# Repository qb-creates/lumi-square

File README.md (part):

# LumiSquare
LumiSquare is a handheld 4x4 LED button game console built around an ATSAMD21J18A. Each of the sixteen silicone pads sits on top of its own RGB LED, and a single 16-channel constant-current driver paints all forty-eight color channels through a column-multiplexed matrix. The console ships with three games, spoken score readout through a DFPlayer Mini, a tone buzzer for note feedback, and a USB-C rechargeable power path that lets the device be played while it charges.

- Project Video (YouTube): https://youtu.be/QTP0zEY1d-M?si=SdRo0hkOKRWzujol
- Multiplexed Display: https://en.wikipedia.org/wiki/Multiplexed_display
- Keyboard Matrix Circuit (diode anti-ghosting): https://en.wikipedia.org/wiki/Keyboard_matrix_circuit
- STP16CPC05 Constant Current LED Driver: https://www.st.com/en/power-management/stp16cpc05.html
- DFPlayer Mini Documentation: https://wiki.dfrobot.com/DFPlayer_Mini_SKU_DFR0299

<div align="center">
	
</div>

## Table of Contents
1. [Software Used](#software)
2. [Main Control Board Circuit](#maincontrolboard)
    - [Power Path and Battery Charging](#powerpath)
    - [LED Button Matrix Driver](#leddriver)
    - [Button Matrix Circuit](#buttonmatrixcircuit)
    - [Buzzer Control](#buzzercontrol)
    - [DF Player Mini](#dfplayer)
    - [Game Firmware](#gamefirmware)
        - [Simon](#simon)
        - [Memory Matching](#memorymatching)
        - [Light Dash](#lightdash)
    - [Power Consumption](#powerconsumption)
    - [Charging Notes](#charging)
    - [Parts List](#partslist)
    - [Schematics](#schematics)
    - [PCB Images](#pcbimages)
3. [Pin Mapping](#pinmapping)
    - [DF Player Mini](#dfplayerpins)
    - [Buzzer](#buzzerpins)
    - [LED Mapping](#ledmapping)
    - [4x4 Button Mapping](#buttonmapping)
4. [STL Viewer](#stlviewer)
    - [Full Design](#fulldesign)
    - [Face Plate](#faceplate)
    - [Back Cover](#backcover)
    - [Main Body](#mainbody)
    - [Main Control Board](#maincontrolboardstl)

## 1. Software Used
- VSCode: https://code.visualstudio.com
- OpenOCD (Arm GDB Bridge): https://openocd.org/pages/about.html
- Arm GNU Toolchain (programming and debugging): https://developer.arm.com/tools-and-software/gnu-toolchain
- KiCad (PCB Design): https://www.kicad.org
- Autodesk Fusion (Parts Design): https://www.autodesk.com/products/fusion-360/overview

The firmware is a CMake project with two presets. `cmake_generate_debug` / `cmake_build_debug` cross compile for the SAMD21 with `arm-none-eabi-gcc` (Cortex-M0+, `F_CPU=48000000`) and emit an `.elf`, `.hex`, and `.bin`. `cmake_generate_desktop` / `cmake_build_desktop` build the same game code as a desktop executable with `DESKTOP_SIMULATION` defined, which swaps the SAMD21 hardware layer for an ImGui/GLFW/miniaudio implementation so the games, LED colors, and audio can be developed without the board. Flashing and debugging is done over the Samtec FTSH-105 SWD header using OpenOCD as the GDB bridge for `arm-none-eabi-gdb`.

## 2. Main Control Board Circuit
The main control board carries everything except the switches and LEDs themselves: the USB-C charger, the battery power path, both boost converters, the 3.3 V regulator, the SAMD21, the LED driver and its column drivers, the tone buzzer, and the DFPlayer Mini. It connects to the button matrix board through two 12-pin headers, one carrying the twelve LED cathode channels and one carrying the four button rows, four button columns, and four LED column anodes.

<div align="center">
 <table>
     <tr>
         <td></td>
         <td></td>
     </tr>
     <tr>
         <td></td>
         <td></td>
     </tr>
 </table>
</div>

### Power Path and Battery Charging
The board runs from either a single cell LiPo or USB-C, and the two sources are kept electrically separate so the device can be used while it charges.

Charging is handled by an MCP73831-2-OT (U1) off the USB-C VBUS rail. The USB-C receptacle is a power-only 6-pin part with the two 5.1k CC pulldowns (R1, R2) needed to advertise a sink. The charge current is set by the PROG resistor:

- Charge current = 1000 V / R3 = 1000 V / 10 kohm = 100 mA

A status LED (D1) with a 330 ohm series resistor (R4) is driven from the STAT pin.

The power path itself is built from two TLV61070A boost converters and a P-channel pass device:

- Q2 (IRLML2246) sits between the battery and the battery-side boost converter. Its gate is tied to the 5 V USB rail and pulled to ground through R11 (220k). With no USB present the gate sits at 0 V and the MOSFET conducts; when USB is plugged in the gate is pulled to 5 V and the battery is disconnected from the system load.
- U3 (TLV61070A) is the battery boost converter. Its enable pin is pulled up to the battery through R6 (150k) and is gated two ways: a TPS3840 (U2) supervisor pulls it low on battery undervoltage, and Q1 (IRLML6244) pulls it low whenever the 5 V USB rail is present.
- U4 (TLV61070A) is the USB boost converter. Its enable pin is tied to its own input, so it runs whenever USB power is present.
- Both converters use a 4.7uH inductor and the same 720k/80k feedback divider, and their outputs are combined onto the 5.3 V rail through Schottky diodes (D2, D3, 1N5819HW-7-F) with 300uF of bulk capacitance (C8, C9, C10).

Downstream of the 5.3 V rail, SW1 is the system power switch feeding a MIC5225-3.3YM5 (U8) that produces the +3.3 V Main rail for the SAMD21, the DFPlayer Mini, and the buzzer. The 5.3 V rail itself powers the LED column drivers, so the RGB LEDs get their headroom from the boost output rather than the regulated logic rail.

### LED Button Matrix Driver
Sixteen common-anode RGB LEDs are driven as a 4x4 multiplexed matrix. Anodes are shared per column, and cathodes are shared per row and color, which reduces forty-eight LED channels down to twelve driver channels plus four column selects.

The cathode side is an STP16CPC05MTR (U6) constant-current sink. Twelve of its sixteen channels are used, one for each row and color combination, and a 200 ohm resistor (R12) on R-EXT sets the per-channel current for all of them. The MCU talks to it over SERCOM4 in SPI master mode (MSB first, 16 bits per update), with a separate GPIO line used to pulse the latch.

The anode side is a high-side switch per column. Each column select from the MCU drives an MMBT3904 (Q4-Q7) through a 2.2k base resistor with a 47k pulldown; the transistor pulls the gate of a TSM680P06CH P-channel MOSFET (Q15-Q18) down against a 100k pullup to the 5.3 V rail, and the MOSFET drain feeds that column's anode line.

Color depth comes from binary code modulation rather than a per-channel PWM peripheral. Each LED stores its color as eight bit planes in `ledColorData[column][row][plane]`. `refreshLeds()` services one LED per call: it enables that LED's column, then shifts out all eight planes back to back, holding plane *i* for 2^i NOP loops so the planes carry the same weighting as the bits of an 8-bit value. After the last plane the driver is cleared to `0x0000` and the next LED index is selected. Only one column ever sources current at a time, and the sixteen LED slots repeat fast enough that the display looks continuous.

Per-LED intensity is a scale from 0 to 1 applied to the color before the bit planes are rebuilt, so the games can dim a pad (the idle Simon pads sit at 0.2 intensity, for example) without changing its color.

### Button Matrix Circuit
The button matrix board holds the sixteen switches, the sixteen RGB LEDs, and nothing else. Switches are wired as a standard 4x4 matrix with a 1N4148 diode in series with every switch (D1-D16) so that simultaneous presses cannot ghost onto unrelated rows. The MCU drives one column low at a time and reads the four row inputs, which are held high by internal pullups, so a pressed button reads as a logic low on its row while its column is active.

The LEDs on this board are wired to match. Anodes are commoned per column (LED_COL1 through LED_COL4) and cathodes are commoned per row and color (LED_R1/G1/B1 through LED_R4/G4/B4). Both groups leave the board on 12-pin headers that mate with the main control board.

**Assembly notes for the button pad:**

- The 4x4 silicone button pad in the parts list is not the right size for this enclosure. The individual pads have to be cut out of the sheet and placed into the pockets in the face plate.
- If you have the button matrix board fabricated, order it with an immersion gold (ENIG) finish. The exposed contact pads need a gold surface for the conductive pill on the bottom of each silicone button to make reliable contact.
- If the board is made with a plain finish instead, buy the copper tape listed in the parts list and adhere a piece to the bottom of each button pad so that the button can bridge the traces.

### Buzzer Control
Tones are produced by a magnetic transducer (BZ2, RDT-4.000-1375-NS1) switched on the low side by an MMBT3904 (Q8). The base is driven through a 2.2k resistor (R22) from the MCU, and a 1N4148W (D4) across the transducer clamps the inductive kickback back into the +3.3 V rail.

The drive signal is hardware PWM from TC7 on PB23. TC7 runs from the 48 MHz main clock with a divide-by-256 prescaler in match PWM mode:

- Timer clock = 48 MHz / 256 = 187.5 kHz
- Output frequency = 187500 / (CC0 + 1)
- `CC1` is always set to `CC0 / 2`, which holds the duty cycle at 50 percent regardless of pitch

Because the period register alone determines pitch, the `MusicNote` enum stores CC0 values directly instead of frequencies. For example `MusicNote::C4 = 716`, which gives 187500 / 717 = 261.5 Hz. Starting and stopping a note is just enabling or disabling the timer, so note timing stays exact while the game loop is busy elsewhere.

### DF Player Mini
Spoken audio comes from a DFPlayer Mini (DFR0299) running off the +3.3 V rail, with its speaker outputs broken out to a JST connector. The module is driven from SERCOM5 in USART mode on PA20/PA21 at 9600 baud.

Every DFPlayer command is a fixed 10-byte frame (`0x7E 0xFF 0x06 <cmd> 0x00 <param hi> <param lo> <checksum hi> <checksum lo> 0xEF`). Rather than building those frames at runtime, the firmware stores all of them precomputed in a constant table, so playing a clip is a table lookup. Frames are pushed out by DMAC channel 0 triggered off the SERCOM5 transmit event, one beat per trigger, so the game loop never blocks on the UART.

Replies come back through the SERCOM5 receive interrupt, which buffers the module's 20-byte response (the command acknowledgement plus the playback-finished frame) and fires a completion callback when the terminating `0xEF` arrives. That callback is what advances queued voice-over sequences, which is how the console reads a multi-digit score back as separate clips.

Audio content is organized into four folders on the SD card, and the command table plays from them by folder and track number:

| Folder | Contents |
|:--|:--|
| 01 | Digits 0 through 9 |
| 02 | 10 through 20, then 30, 40, 50, 60, 70, 80, 90 |
| 03 | 100, 200, 300, 400, 500 |
| 04 | Phrases: "your score is", "new high score", the game names, the difficulty names, countdown, mute, unmute |

To read a score such as 342, the firmware queues the hundreds clip, then the tens clip, then the ones clip, and lets the completion callback chain them together. Volume is set with command `0x06`; the unmute command sends a value of 25, and muting sends a value of 0.

### Game Firmware
The firmware is a fixed-timestep game engine. TC3 runs from the 48 MHz clock with a divide-by-1024 prescaler and is preloaded so it overflows every 16 ms, giving a 62.5 Hz update rate. The main loop looks like this:

```cpp
while (true)
{
    LEDMatrix::refreshLeds();

    if (!DeviceUtility::fixedUpdate)
        continue;

    DeviceUtility::fixedUpdate = false;
    Input::pollButtons();

    StateManager::Instance().onFixedUpdate();
    AudioSource::Instance().onFixedUpdate();
    ShutdownUtility::Instance().onFixedUpdate();
    SerialCommandManager::Instance().onFixedUpdate();
}
```

LED refresh runs as fast as the CPU allows, while everything else is gated on the 16 ms tick. All game timers are expressed in milliseconds and decremented by `DeviceUtility::DELTA_TIME`, so game speed is independent of how quickly the LED refresh happens to be running.

All hardware access goes through an abstract `DeviceUtility` singleton. `SAMD21J18Utility` implements it against the real peripherals, and `DesktopUtility` implements the same interface with ImGui, GLFW, and miniaudio. Every layer above it (games, LED matrix, input, audio, scoring) is shared between the two builds.

Game flow is a state machine. `StateManager` holds one instance of each state and dispatches `enterState`, `updateState`, `exitState`, and `onButtonPressed` to whichever one is current:

| State | Purpose |
|:--|:--|
| PowerOn | Startup animation and audio |
| Menu | Game selection, difficulty selection, mute toggle, start countdown |
| MemoryMatching | Color pair matching game |
| Simon | Sequence memorization game |
| LightDash | Timed reaction game |
| GameOver | Score readout and high score announcement |

In the menu, the Next and Previous buttons cycle through the three games and the Difficulty button cycles Easy, Medium, Hard. Holding the Difficulty button for one second toggles mute instead of changing difficulty, and the new mute state is announced through the DFPlayer. Selecting a game plays a spoken 3-2-1 countdown before the state switch.

`ScoreManager` tracks the current score and a high score per game and per difficulty in a 6x3 matrix. Persistence is handled by `StorageService`, which keeps high scores in the SAMD21's own flash instead of an external EEPROM. The linker script carves the last 1 KB of the 256 KB flash out of the `rom` region and gives it its own memory region:

```
rom      (rx)  : ORIGIN = 0x00000000, LENGTH = 0x0003FC00
eeprom   (rx)  : ORIGIN = 0x0003FC00, LENGTH = 0x00000400
```

A matching `.eeprom` output section is mapped into that region, and the high score array is placed there with `__attribute__((__section__(".eeprom")))`, so the linker will never let program code grow into the saved data. Each high score is a single byte addressed by game and difficulty: Memory Matching at offset 0, Simon at offset 6, Light Dash at offset 12, plus the difficulty index. A byte that has never been written reads back as `0xFF` and is reported as a score of zero.

Reading a high score is a direct pointer dereference into that flash region. Writing has to respect the SAMD21's flash granularity, so saving one byte means copying the surrounding 256-byte row into RAM, patching the byte, erasing the row through NVMCTRL, and writing all four 64-byte pages back. The read and write bodies are commented out in `StorageService` at the moment, so high scores currently live in RAM until they are re-enabled.

#### Simon
The console plays a growing sequence of lit pads with a distinct note per pad, and the player repeats it. Only eight of the sixteen pads are playable. On Easy the four center pads are used (indexes 5, 6, 9, 10); on Medium and Hard the four corners (0, 3, 12, 15) are added. Each playable pad has a fixed note assignment:

| Pad Index | Note | Pad Index | Note |
|:--:|:--:|:--:|:--:|
| 5 | G4 | 4 | A4 |
| 6 | C4 | 7 | D4 |
| 9 | E4 | 8 | F4 |
| 10 | G3 | 11 | B3 |

The player gets three lives on Easy and Medium and a single life on Hard. Idle pads sit at 0.2 intensity and the active pad steps up to full intensity for each sequence element, so the sequence reads clearly without the board going dark between steps.

#### Memory Matching
Eight color pairs are shuffled across the sixteen pads at the start of the round. Pressing a pad lights it in its hidden color; pressing a second pad evaluates the guess. Matched pairs stay lit, mismatched pads fade back off after a short reveal timer, and the round ends once all eight matches are found. Selection and evaluation are confirmed with C5 and D5 tones.

#### Light Dash
A 30 second timed reaction round. Five pads start lit in turquoise, and every lit pad carries its own randomized turn-off timer. Hitting a lit pad scores a point and immediately lights a new random pad; hitting a dark pad deducts points and plays a low B3. Difficulty changes the pressure directly:

| Difficulty | LED Turn-Off Window | Score Deduction | Bonus Pad Value | Bonus Window | Power-Ups |
|:--|:--:|:--:|:--:|:--:|:--:|
| Easy | 1500 - 2500 ms | -1 | 5 | 400 ms | Disabled |
| Medium | 1000 - 2000 ms | -2 | 3 | 500 ms | Enabled |
| Hard | 750 - 1200 ms | -3 | 5 | 400 ms | Enabled |

### Power Consumption
This power system was sized around continuous play with the LED matrix, the DFPlayer Mini, and the buzzer all active, measured on the finished assembly rather than estimated from datasheet maximums.

Measured load envelope:

- USB input, playing while charging: ~170 mA typical, 200 mA maximum
- Battery draw with USB disconnected: ~100 mA typical, 120 mA maximum
- Programmed battery charge current (MCP73831 with a 10k PROG resistor): 100 mA

The USB figure is the total of both jobs at once: the system load through the USB boost converter plus the 100 mA going into the battery. Against the 500 mA available from a standard USB port:

- Worst-case USB draw: 0.20 A of the 0.50 A available
- Remaining headroom: 0.30 A, roughly 40 percent port utilization

Battery capability and runtime with a 750 mAh single cell LiPo:

- Typical: 750 mAh / 100 mA = 7.5 h
- Worst case: 750 mAh / 120 mA = 6.25 h

That works out to roughly 6 to 7.5 hours of continuous play per charge, with the practical number landing near the low end of that range because the boost converter draws more input current as the cell voltage falls toward its cutoff. A full recharge from empty at 100 mA takes about 8 hours once the constant-voltage taper at the end of the charge cycle is included.

Conclusion: the USB port has roughly 300 mA of unused headroom even in the worst case, so charging and full-brightness play can happen at the same time without exceeding what a standard port supplies.

### Charging Notes
The device can be safely used while charging due to its power-path design. When USB power is connected, the battery-powered boost converter is disabled and the battery is isolated from the system load, allowing it to charge independently at 100 mA. The system is powered through a separate boost converter from USB power during this time. Since the combined system load and charging current remain well below the 500 mA available from a standard USB port, normal operation can continue while the battery is charging.

---
### Parts List
<div align="center">
    <table>
        <tr>
            <td valign="top">
                <table>
                    <tr><th>Part Number</th><th>Quantity</th></tr>
                    <tr><td><a href="https://www.amazon.com/dp/B0B21B262L?ref=ppx_yo2ov_dt_b_fed_asin_title&amp;th=1">4.2V Lipo</a></td><td align="center">x1</td></tr>
                    <tr><td><a href="https://www.digikey.com/en/products/detail/jst-sales-america-inc/S2B-PH-SM4-TB/926655">S2B-PH-SM4-TB</a></td><td align="center">x1</td></tr>
                    <tr><td><a href="https://www.digikey.com/en/products/detail/raltron-electronics/RDT-4-000-1375-NS1/22320849">RDT-4.000-1375-NS1</a></td><td align="center">x1</td></tr>
                    <tr><td><a href="https://www.digikey.com/en/products/detail/samsung-electro-mechanics/CL10A475KP8NNNC/3886702">4.7uF Capacitor</a></td><td align="center">x2</td></tr>
                    <tr><td><a href="https://www.digikey.com/en/products/detail/kyocera-avx/TPCL105M010R5000/1472496">1uF Tantalum Capacitor</a></td><td align="center">x3</td></tr>
                    <tr><td><a href="https://www.digikey.com/en/products/detail/taiyo-yuden/TMK107B7105KA-T/2714162">1uF Capacitor</a></td><td align="center">x2</td></tr>
                    <tr><td><a href="https://www.digikey.com/en/products/detail/murata-electronics/GCM31CR71C106KA64K/2592432">10uF Capacitor</a></td><td align="center">x2</td></tr>
                    <tr><td><a href="https://www.digikey.com/en/products/detail/murata-electronics/GCM31CR70J226ME23L/2592428">22uF Capacitor</a></td><td align="center">x2</td></tr>
                    <tr><td><a href="https://www.digikey.com/en/products/detail/kyocera-avx/TAJC107K010RNJ/563809">100uF Capacitor</a></td><td align="center">x3</td></tr>
                    <tr><td><a href="https://www.digikey.com/en/products/detail/kemet/C0603C102K5RACTU/411081">.001uF Capacitor</a></td><td align="center">x1</td></tr>
                    <tr><td><a href="https://www.digikey.com/en/products/detail/kemet/C0603C103K5RACTU/411090">.01uF Capacitor</a></td><td align="center">x1</td></tr>
                    <tr><td><a href="https://www.digikey.com/en/products/detail/kemet/C0603C104K3RACTU/416044">.1uF Capacitor</a></td><td align="center">x6</td></tr>
                    <tr><td><a href="https://www.digikey.com/en/products/detail/murata-electronics/GRM188R61E225KA12D/4905349">2.2uF Capacitor</a></td><td align="center">x1</td></tr>
                    <tr><td>LED</td><td align="center">x2</td></tr>
                    <tr><td><a href="https://www.digikey.com/en/products/detail/diodes-incorporated/1N5819HW-7-F/814970">1N5819HW-7-F Diode</a></td><td align="center">x2</td></tr>
                    <tr><td><a href="https://www.digikey.com/en/products/detail/smc-diode-solutions/1N4148W/6022450">1N4148W Diode</a></td><td align="center">x1</td></tr>
                    <tr><td><a href="https://www.amazon.com/2-54mm-Breakaway-Female-Connector-Arduino/dp/B01MQ48T2V/ref=sr_1_2_sspa?crid=16L90K4M3IPUJ&amp;dib=eyJ2IjoiMSJ9.PiVZGqfONIcta-M5ftDeSQvccVRmw9BxQL2rt7zLLUlXX1aAbZE0DyQvFnNRSX7J1oJEA5hJfbgi6EJ3rHkMxb469SjCBiPbG4t4CkfheX_9W7Yiw4iFecXODu6yRoJ7FvokpWTZ5C9jK1dhZLU-0gXDsoVq96wH-NXO7UmstsQCzrZOSzCfbpis861lxSzX91fkbaxrOKRMrX-EQ3cjwH1Og4xyfn4PJ6o445uHR2s.cW7WMcxh5mXZc1T8bR0I8nLIh45-W5JJZGus4sUdDDI&amp;dib_tag=se&amp;keywords=Male+headers&amp;qid=1783892715&amp;sprefix=male+header%2Caps%2C141&amp;sr=8-2-spons&amp;sp_csd=d2lkZ2V0TmFtZT1zcF9hdGY&amp;psc=1">Conn_01x12</a></td><td align="center">x2</td></tr>
                    <tr><td><a href="https://www.digikey.com/en/products/detail/gct/USB4125-GF-A/13547388">USB_C_Receptacle_PowerOnly_6P</a></td><td align="center">x1</td></tr>
                    <tr><td><a href="https://www.digikey.com/en/products/detail/samtec-inc/FTSH-105-01-L-DV-K/1875039">FTSH-105-01-X-DV-P-K-X</a></td><td align="center">x1</td></tr>
                    <tr><td><a href="https://www.digikey.com/en/products/detail/bourns-inc/SRP3020TA-4R7M/9350997">4.7uH</a></td><td align="center">x2</td></tr>
                    <tr><td><a href="https://www.digikey.com/en/products/detail/infineon-technologies/IRLML6244TRPBF/2393871">IRLML6244</a></td><td align="center">x1</td></tr>
                    <tr><td><a href="https://www.digikey.com/en/products/detail/umw/UMWIRLML2246TR/24889419">UMWIRLML2246TRCT</a></td><td align="center">x2</td></tr>
                    <tr><td><a href="https://www.digikey.com/en/products/detail/onsemi/MMBT3904LT1G/919601">MMBT3904</a></td><td align="center">x5</td></tr>
                    <tr><td><a href="https://www.digikey.com/en/products/detail/taiwan-semiconductor-corporation/TSM680P06CH-X0G/7360503">TSM680P06CH</a></td><td align="center">x4</td></tr>
                    <tr><td><a href="https://www.digikey.com/en/products/detail/yageo/RC0603FR-075K1L/727268">5.1k ohm Resistor</a></td><td align="center">x2</td></tr>
                    <tr><td><a href="https://www.digikey.com/en/products/detail/stackpole-electronics-inc/RMCF0603JT10K0/1758104">10k ohm Resistor</a></td><td align="center">x2</td></tr>
                    <tr><td><a href="https://www.digikey.com/en/products/detail/yageo/RC0603FR-07330RL/727162">330 ohm Resistor</a></td><td align="center">x2</td></tr>
                    <tr><td><a href="https://www.digikey.com/en/products/detail/yageo/RC0603JR-071K3L/726686">1.3k ohm Resistor</a></td><td align="center">x1</td></tr>
                    <tr><td><a href="https://www.digikey.com/en/products/detail/koa-speer-electronics-inc/RK73B1JTTD154J/9844780">150k ohm Resistor</a></td><td align="center">x1</td></tr>
                </table>
            </td>
            <td width="24"></td>
            <td valign="top">
                <table>
                    <tr><th>Part Number</th><th>Quantity</th></tr>
                    <tr><td><a href="https://www.digikey.com/en/products/detail/yageo/RC0603FR-07715KL/727372">720k ohm Resistor</a></td><td align="center">x2</td></tr>
                    <tr><td><a href="https://www.digikey.com/en/products/detail/yageo/RC0603JR-0775KL/726828">80k ohm Resistor</a></td><td align="center">x2</td></tr>
                    <tr><td><a href="https://www.digikey.com/en/products/detail/stackpole-electronics-inc/RMCF0603FT220K/1760805">220k ohm Resistor</a></td><td align="center">x1</td></tr>
                    <tr><td><a href="https://www.digikey.com/en/products/detail/rohm-semiconductor/ESR03EZPF2000/1983436">200 ohm Resistor</a></td><td align="center">x1</td></tr>
                    <tr><td><a href="https://www.digikey.com/en/products/detail/yageo/RC0603FR-07100KL/726889">100k ohm Resistor</a></td><td align="center">x5</td></tr>
                    <tr><td><a href="https://www.digikey.com/en/products/detail/panasonic-industry/ERA-3AEB153V/1465882">15k ohm Resistor</a></td><td align="center">x3</td></tr>
                    <tr><td><a href="https://www.digikey.com/en/products/detail/yageo/RC0603FR-072K2L/727016">2.2k ohm Resistor</a></td><td align="center">x5</td></tr>
                    <tr><td><a href="https://www.digikey.com/en/products/detail/yageo/RC0603FR-0747KL/727253">47k ohm Resistor</a></td><td align="center">x4</td></tr>
                    <tr><td><a href="https://www.amazon.com/2-54mm-Breakaway-Female-Connector-Arduino/dp/B01MQ48T2V/ref=sr_1_2_sspa?crid=16L90K4M3IPUJ&amp;dib=eyJ2IjoiMSJ9.PiVZGqfONIcta-M5ftDeSQvccVRmw9BxQL2rt7zLLUlXX1aAbZE0DyQvFnNRSX7J1oJEA5hJfbgi6EJ3rHkMxb469SjCBiPbG4t4CkfheX_9W7Yiw4iFecXODu6yRoJ7FvokpWTZ5C9jK1dhZLU-0gXDsoVq96wH-NXO7UmstsQCzrZOSzCfbpis861lxSzX91fkbaxrOKRMrX-EQ3cjwH1Og4xyfn4PJ6o445uHR2s.cW7WMcxh5mXZc1T8bR0I8nLIh45-W5JJZGus4sUdDDI&amp;dib_tag=se&amp;keywords=Male+headers&amp;qid=1783892715&amp;sprefix=male+header%2Caps%2C141&amp;sr=8-2-spons&amp;sp_csd=d2lkZ2V0TmFtZT1zcF9hdGY&amp;psc=1">SW_SPST</a></td><td align="center">x1</td></tr>
                    <tr><td><a href="https://www.digikey.com/en/products/detail/jst-sales-america-inc/SM02B-NSHSS-TB/3313627">SM02B-NSHSS-TB</a></td><td align="center">x1</td></tr>
                    <tr><td><a href="https://www.amazon.com/dp/B0FD32HBD2?ref=ppx_yo2ov_dt_b_fed_asin_title">JST SH 1.0mm 2-Pin Connector Male</a></td><td align="center">x6</td></tr>
                    <tr><td><a href="https://www.digikey.com/en/products/detail/jst-sales-america-inc/BM02B-SRSS-TB/926694">455-1788-1-ND</a></td><td align="center">x6</td></tr>
                    <tr><td><a href="https://www.digikey.com/en/products/detail/e-switch/TL3342F260QG/4029402">TL3342F260QG</a></td><td align="center">x1</td></tr>
                    <tr><td><a href="https://www.amazon.com/dp/B07FS9CLHB?ref=ppx_yo2ov_dt_b_fed_asin_title">SW_Push</a></td><td align="center">x3</td></tr>
                    <tr><td><a href="https://www.digikey.com/en/products/detail/microchip-technology/MCP73831T-4ADI-OT/1874437">MCP73831-2-OT</a></td><td align="center">x1</td></tr>
                    <tr><td><a href="https://www.digikey.com/en/products/detail/texas-instruments/TPS3840DL35DBVR/15857118">TPS3840</a></td><td align="center">x1</td></tr>
                    <tr><td><a href="https://www.digikey.com/en/products/detail/texas-instruments/TLV61070ADBVR/16982069">TLV61070A</a></td><td align="center">x2</td></tr>
                    <tr><td><a href="https://www.digikey.com/en/products/detail/microchip-technology/ATSAMD21J18A-AUT/4878863">ATSAMD21J18A-A</a></td><td align="center">x1</td></tr>
                    <tr><td><a href="https://www.digikey.com/en/products/detail/stmicroelectronics/STP16CPC05MTR/2021162">STP16CPC05MTR</a></td><td align="center">x1</td></tr>
                    <tr><td><a href="https://www.digikey.com/en/products/detail/microchip-technology/MIC5225-3-3YM5-TR/1815447">MIC5225-3.3YM5</a></td><td align="center">x1</td></tr>
                    <tr><td><a href="https://www.amazon.com/dp/B09YGDQV3Z?ref=ppx_yo2ov_dt_b_fed_asin_title&amp;th=1">Speaker</a></td><td align="center">x1</td></tr>
                    <tr><td><a href="https://www.amazon.com/HiLetgo-Arduino-Player-Module-DFPlayer/dp/B01D1D0E7Q/ref=sr_1_2_sspa?crid=1M2VND5DUGHIK&amp;dib=eyJ2IjoiMSJ9.YrXsgIIjUaSsAEXykz_XhedAiNLuph_OWmxQmAavccnvR6je_SPV6UBJCTTjR1HUEWpdZX6tAgtMeH9srEe7P_8sLd3BhB1FnESxTUJ68ddGd1M1iRmT9N21VSjNgaNmsWCMiqy5aJ65WuFNIvULsRhTw6QEZZM6lOIUVj8uBlg-XCqs1zCrPYvssHCZ58nAGFlbAthMA-R4jTEtol9RGDQelZQMH3D_3LqgZeJn3uU.FTGOfaaoE_vI-eDcVBTyS0GOEBdRKrRR-P7t4EqJue8&amp;dib_tag=se&amp;keywords=dfplayer+mini&amp;qid=1783881948&amp;sprefix=dfplayermini%2Caps%2C240&amp;sr=8-2-spons&amp;sp_csd=d2lkZ2V0TmFtZT1zcF9hdGY&amp;psc=1">DFPLayerMini</a></td><td align="center">x1</td></tr>
                    <tr><td><a href="https://www.sparkfun.com/button-pad-4x4-led-compatible.html">Button Pad</a></td><td align="center">x1</td></tr>
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
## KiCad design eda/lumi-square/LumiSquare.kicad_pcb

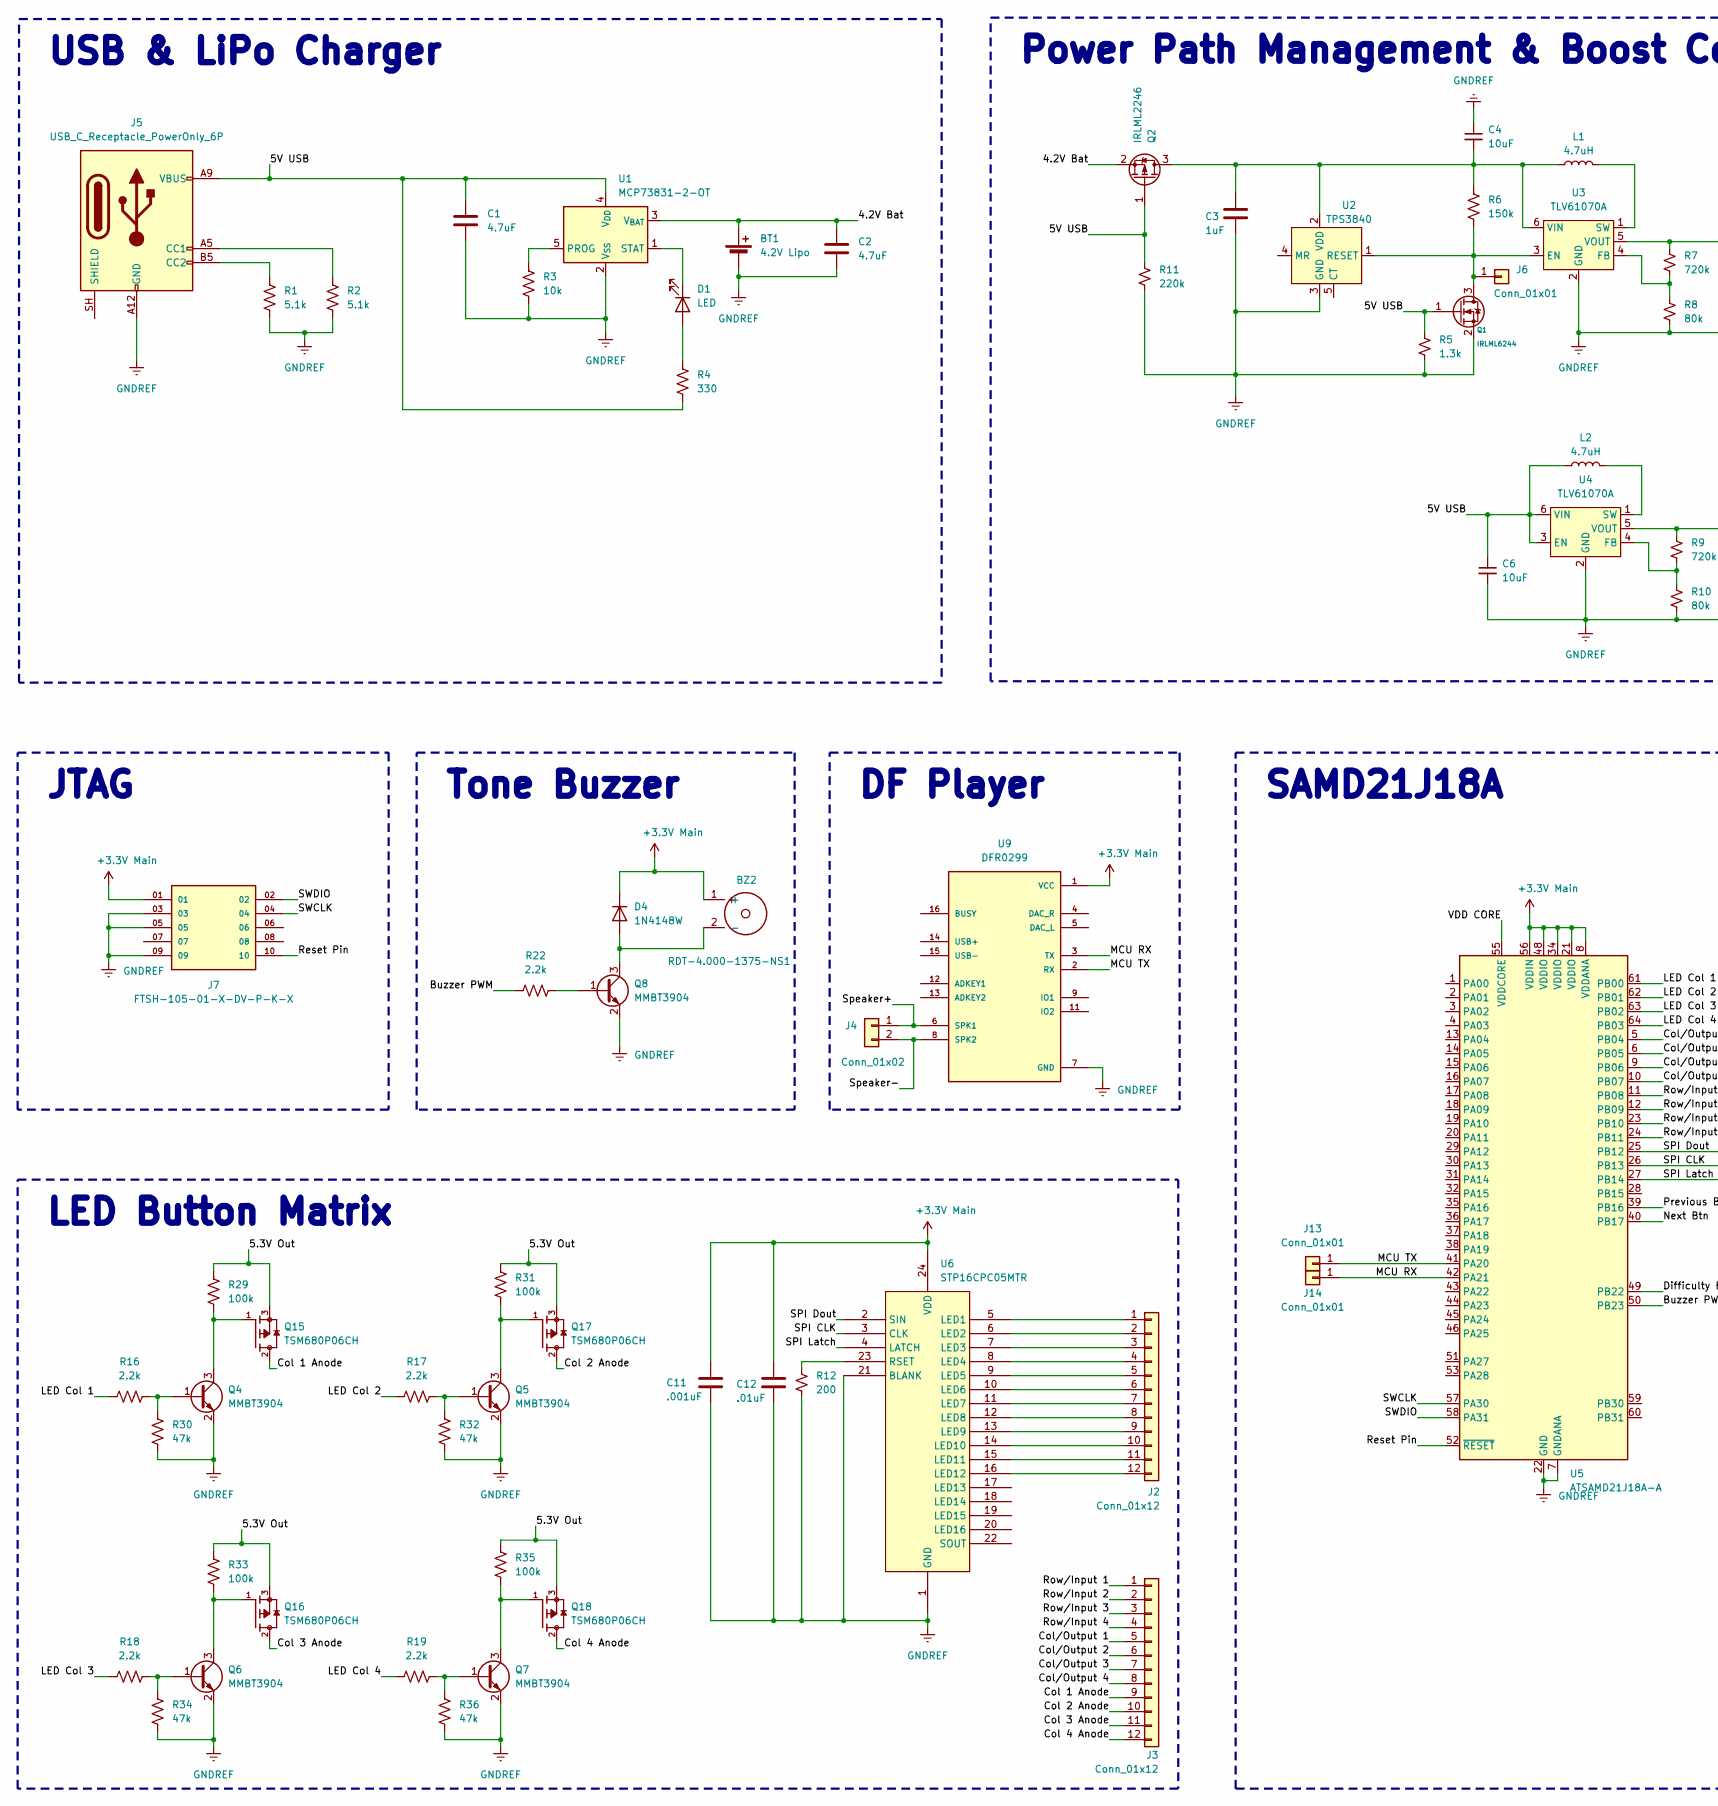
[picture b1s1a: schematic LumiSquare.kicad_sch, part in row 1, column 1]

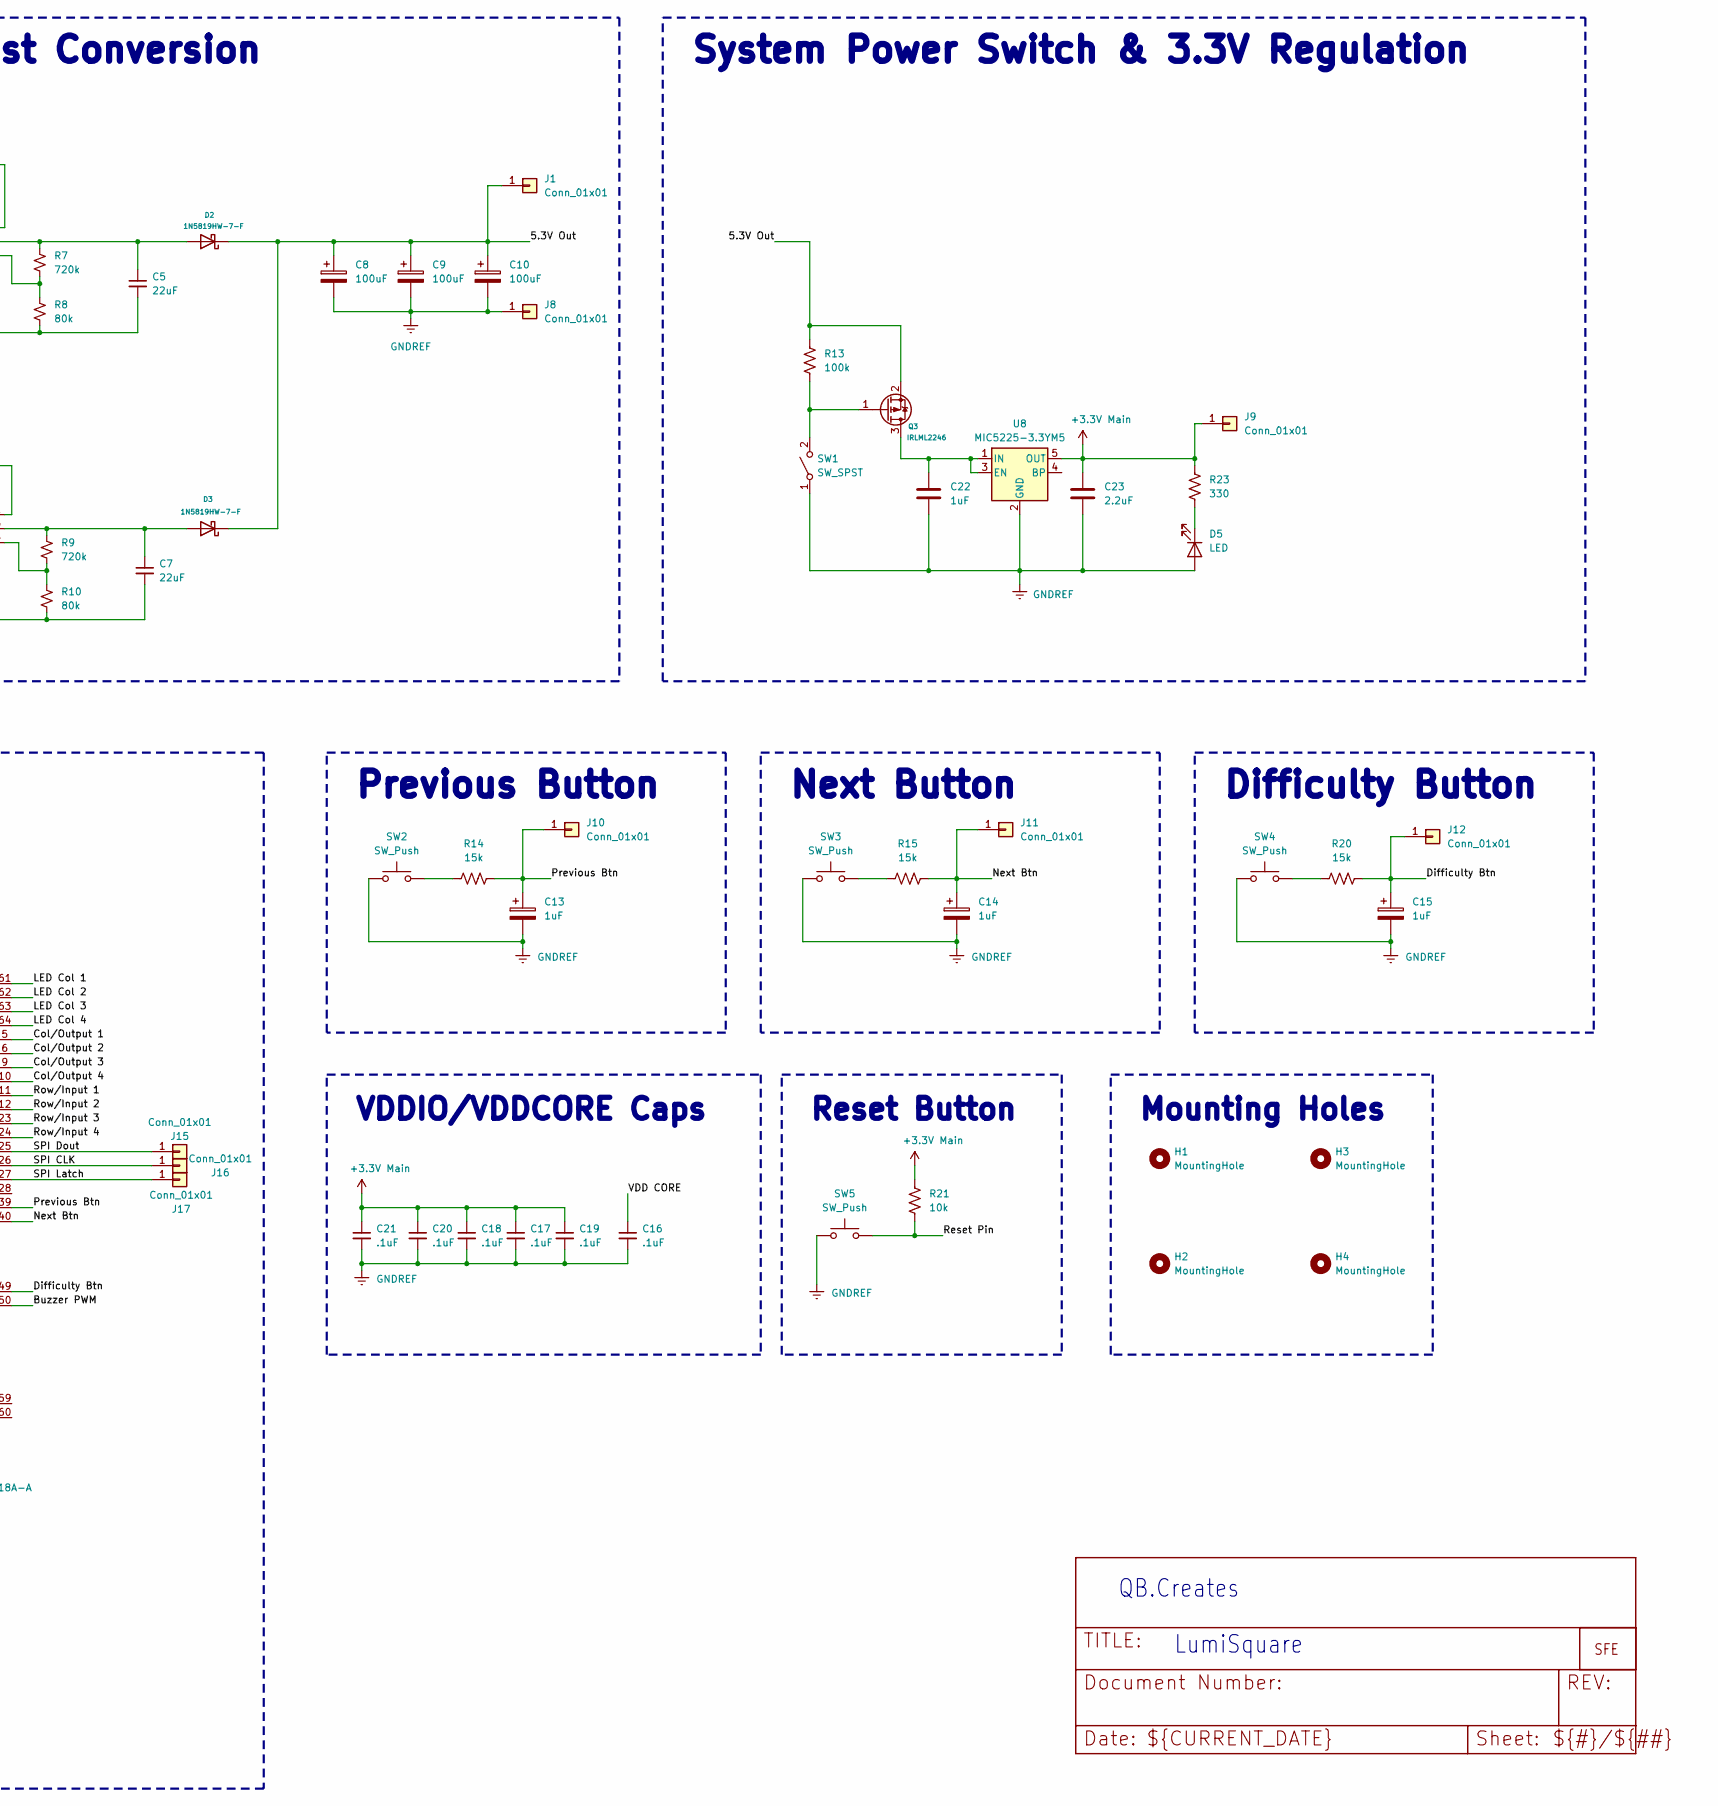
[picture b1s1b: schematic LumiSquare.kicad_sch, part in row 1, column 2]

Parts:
BT1: 4.2V Lipo; JST_PH_S2B-PH-SM4-TB_1x02-1MP_P2.00mm_Horizontal
BZ2: RDT-4.000-1375-NS1
C1, C2: 4.7uF; C_0603_1608Metric_Pad1.08x0.95mm_HandSolder
C3, C13, C14, C15, C22: 1uF; C_0603_1608Metric_Pad1.08x0.95mm_HandSolder
C4, C6: 10uF; C_1206_3216Metric
C5, C7: 22uF; C_1206_3216Metric
C8, C9, C10: 100uF; CP_EIA-6032-28_Kemet-C_HandSolder
C11: .001uF; C_0603_1608Metric_Pad1.08x0.95mm_HandSolder
C12: .01uF; C_0603_1608Metric_Pad1.08x0.95mm_HandSolder
C16, C17, C18, C19, C20, C21: .1uF; C_0603_1608Metric_Pad1.08x0.95mm_HandSolder
C23: 2.2uF; C_0603_1608Metric_Pad1.08x0.95mm_HandSolder
D1, D5: LED; JST_SH_BM02B-SRSS-TB_1x02-1MP_P1.00mm_Vertical
D2, D3: 1N5819HW-7-F; D_SOD-123
D4: 1N4148W; D_SOD-123
H1, H2, H3, H4: MountingHole; MountingHole_2.2mm_M2_DIN965_Pad
J1, J6, J8, J9, J10, J11, J12, J13, J14, J15, J16, J17: Conn_01x01; TestPoint_Pad_D1.0mm
J2, J3: Conn_01x12; PinSocket_1x12_P2.54mm_Vertical
J4: Conn_01x02; JST_SH_SM02B-SRSS-TB_1x02-1MP_P1.00mm_Horizontal
J5: USB_C_Receptacle_PowerOnly_6P; USB_C_Receptacle_GCT_USB4125-xx-x-0190_6P_TopMnt_Horizontal
J7: FTSH-105-01-X-DV-P-K-X; SAMTEC_FTSH-105-01-X-DV-P-K-X; PARTREV H
L1, L2: 4.7uH; Bourns SRP30xx
Q1: IRLML6244; SOT-23
Q2, Q3: IRLML2246; SOT-23
Q4, Q5, Q6, Q7, Q8: MMBT3904; SOT-23
Q15, Q16, Q17, Q18: TSM680P06CH; TO228P680X245X847-3; PARTREV D14
R1, R2: 5.1k; R_0603_1608Metric_Pad0.98x0.95mm_HandSolder
R3, R21: 10k; R_0603_1608Metric_Pad0.98x0.95mm_HandSolder
R4, R23: 330; R_0603_1608Metric_Pad0.98x0.95mm_HandSolder
R5: 1.3k; R_0603_1608Metric_Pad0.98x0.95mm_HandSolder
R6: 150k; R_0603_1608Metric_Pad0.98x0.95mm_HandSolder
R7, R9: 720k; R_0603_1608Metric_Pad0.98x0.95mm_HandSolder
R8, R10: 80k; R_0603_1608Metric
R11: 220k; R_0603_1608Metric_Pad0.98x0.95mm_HandSolder
R12: 200; R_0603_1608Metric_Pad0.98x0.95mm_HandSolder
R13, R29, R31, R33, R35: 100k; R_0603_1608Metric_Pad0.98x0.95mm_HandSolder
R14, R15, R20: 15k; R_0603_1608Metric_Pad0.98x0.95mm_HandSolder
R16, R17, R18, R19, R22: 2.2k; R_0603_1608Metric_Pad0.98x0.95mm_HandSolder
R30, R32, R34, R36: 47k; R_0603_1608Metric_Pad0.98x0.95mm_HandSolder
SW1: SW_SPST; JST_SH_BM02B-SRSS-TB_1x02-1MP_P1.00mm_Vertical
SW2, SW3, SW4: SW_Push; JST_SH_BM02B-SRSS-TB_1x02-1MP_P1.00mm_Vertical
SW5: SW_Push; SW_SPST_TL3342
U1: MCP73831-2-OT; SOT-23-5
U2: TPS3840; SOT-23-5
U3, U4: TLV61070A; SOT-23-6
U5: ATSAMD21J18A-A; TQFP-64_10x10mm_P0.5mm
U6: STP16CPC05MTR; SOIC-24W_7.5x15.4mm_P1.27mm
U8: MIC5225-3.3YM5; SOT-23-5
U9: DFR0299; MODULE_DFR0299
U$1: LOGO-SFE; SFE-NEW-WEBLOGO

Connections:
+3.3V Main: BZ2.1 (+), C11.1, C12.1, C17.1, C18.1, C19.1, C20.1, C21.1, C23.1, D4.1 (K), J7.01, J9.1 (Pin_1_1), R21.1, R23.2, U5.8 (VDDANA), U5.21 (VDDIO), U5.34 (VDDIO), U5.48 (VDDIO), U5.56 (VDDIN), U6.24 (VDD), U8.5 (OUT), U9.1 (VCC)
/4.2V Bat: BT1.1 (+), C2.1, Q2.2 (S), U1.3 (V_{BAT})
/5.3V Out: C8.1, C9.1, C10.1, D2.1 (K), D3.1 (K), J1.1 (Pin_1_1), Q3.2 (S), Q15.3, Q16.3, Q17.3, Q18.3, R13.1, R29.2, R31.2, R33.2, R35.2
/5V USB: C1.1, C6.1, J5.A9 (VBUS), J5.B9 (VBUS), L2.1, Q1.1 (G), Q2.1 (G), R4.1, R5.1, R11.1, U1.4 (V_{DD}), U4.3 (EN), U4.6 (VIN)
/Buzzer PWM: R22.1, U5.50 (PB23)
/Col 1 Anode: J3.9, Q15.2
/Col 2 Anode: J3.10, Q17.2
/Col 3 Anode: J3.11, Q16.2
/Col 4 Anode: J3.12, Q18.2
/Col/Output 1: J3.5, U5.5 (PB04)
/Col/Output 2: J3.6, U5.6 (PB05)
/Col/Output 3: J3.7, U5.9 (PB06)
/Col/Output 4: J3.8, U5.10 (PB07)
/Difficulty Btn: C15.1, J12.1 (Pin_1_1), R20.2, U5.49 (PB22)
/LED Col 1: R16.1, U5.61 (PB00)
/LED Col 2: R17.1, U5.62 (PB01)
/LED Col 3: R18.1, U5.63 (PB02)
/LED Col 4: R19.1, U5.64 (PB03)
/MCU RX: J14.1 (Pin_1_1), U5.42 (PA21), U9.3 (TX)
/MCU TX: J13.1 (Pin_1_1), U5.41 (PA20), U9.2 (RX)
/Next Btn: C14.1, J11.1 (Pin_1_1), R15.2, U5.40 (PB17)
/Previous Btn: C13.1, J10.1 (Pin_1_1), R14.2, U5.39 (PB16)
/Reset Pin: J7.10, R21.2, SW5.2, U5.52 (~RESET)
/Row/Input 1: J3.1, U5.11 (PB08)
/Row/Input 2: J3.2, U5.12 (PB09)
/Row/Input 3: J3.3, U5.23 (PB10)
/Row/Input 4: J3.4, U5.24 (PB11)
/SPI CLK: J16.1 (Pin_1_1), U5.26 (PB13), U6.3 (CLK)
/SPI Dout: J15.1 (Pin_1_1), U5.25 (PB12), U6.2 (SIN)
/SPI Latch: J17.1 (Pin_1_1), U5.27 (PB14), U6.4 (LATCH)
/SWCLK: J7.04, U5.57 (PA30)
/SWDIO: J7.02, U5.58 (PA31)
/Speaker+: J4.1, U9.6 (SPK1)
/Speaker-: J4.2, U9.8 (SPK2)
/VDD CORE: C16.1, U5.55 (VDDCORE)
GNDREF: BT1.2 (-), C1.2, C2.2, C3.2, C4.1, C5.2, C6.2, C7.2, C8.2, C9.2, C10.2, C11.2, C12.2, C13.2, C14.2, C15.2, C16.2, C17.2, C18.2, C19.2, C20.2, C21.2, C22.2, C23.2, D5.2 (A), J5.A12 (GND), J5.B12 (GND), J7.03, J7.05, J7.09, J8.1 (Pin_1_1), Q1.2 (S), Q4.2 (E), Q5.2 (E), Q6.2 (E), Q7.2 (E), Q8.2 (E), R1.2, R2.2, R3.2, R5.2, R8.2, R10.2, R11.2, R12.2, R30.1, R32.1, R34.1, R36.1, SW1.1 (A), SW2.1, SW3.1, SW4.1, SW5.1, U1.2 (V_{SS}), U2.3 (GND), U3.2 (GND), U4.2 (GND), U5.7 (GNDANA), U5.22 (GND), U5.33 (GND), U5.47 (GND), U5.54 (GND), U6.1 (GND), U6.21 (BLANK), U8.2 (GND), U9.7 (GND), U9.10 (GND)
unnamed: BZ2.2 (-), D4.2 (A), Q8.3 (C)
unnamed: D1.2 (A), R4.2
unnamed: D1.1 (K), U1.1 (STAT)
unnamed: C5.1, D2.2 (A), R7.1, U3.5 (VOUT)
unnamed: C7.1, D3.2 (A), R9.1, U4.5 (VOUT)
unnamed: D5.1 (K), R23.1
unnamed: J2.1, U6.5 (LED1)
unnamed: J2.2, U6.6 (LED2)
unnamed: J2.3, U6.7 (LED3)
unnamed: J2.4, U6.8 (LED4)
unnamed: J2.5, U6.9 (LED5)
unnamed: J2.6, U6.10 (LED6)
unnamed: J2.7, U6.11 (LED7)
unnamed: J2.8, U6.12 (LED8)
unnamed: J2.9, U6.13 (LED9)
unnamed: J2.10, U6.14 (LED10)
unnamed: J2.11, U6.15 (LED11)
unnamed: J2.12, U6.16 (LED12)
unnamed: J5.A5 (CC1), R2.1
unnamed: J5.B5 (CC2), R1.1
unnamed: J6.1 (Pin_1_1), Q1.3 (D), R6.2, U2.1 (RESET), U3.3 (EN)
unnamed: C3.1, C4.2, L1.1, Q2.3 (D), R6.1, U2.2 (VDD), U3.6 (VIN)
unnamed: C22.1, Q3.3 (D), U8.1 (IN), U8.3 (EN)
unnamed: Q3.1 (G), R13.2, SW1.2 (B)
unnamed: Q4.1 (B), R16.2, R30.2
unnamed: Q4.3 (C), Q15.1, R29.1
unnamed: Q5.1 (B), R17.2, R32.2
unnamed: Q5.3 (C), Q17.1, R31.1
unnamed: Q6.1 (B), R18.2, R34.2
unnamed: Q6.3 (C), Q16.1, R33.1
unnamed: Q7.1 (B), R19.2, R36.2
unnamed: Q7.3 (C), Q18.1, R35.1
unnamed: Q8.1 (B), R22.2
unnamed: R14.1, SW2.2
unnamed: R15.1, SW3.2
unnamed: R20.1, SW4.2
unnamed: R3.1, U1.5 (PROG)
unnamed: R7.2, R8.1, U3.4 (FB)
unnamed: L1.2, U3.1 (SW)
unnamed: R9.2, R10.1, U4.4 (FB)
unnamed: L2.2, U4.1 (SW)
unnamed: R12.1, U6.23 (RSET)

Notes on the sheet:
USB & LiPo Charger
SAMD21J18A
Mounting Holes
VDDIO/VDDCORE Caps
Reset Button
DF Player
Power Path Management & Boost Conversion
Tone Buzzer
Next Button
System Power Switch & 3.3V Regulation
LumiSquare
Previous Button
JTAG
QB.Creates
LED Button Matrix
Difficulty Button

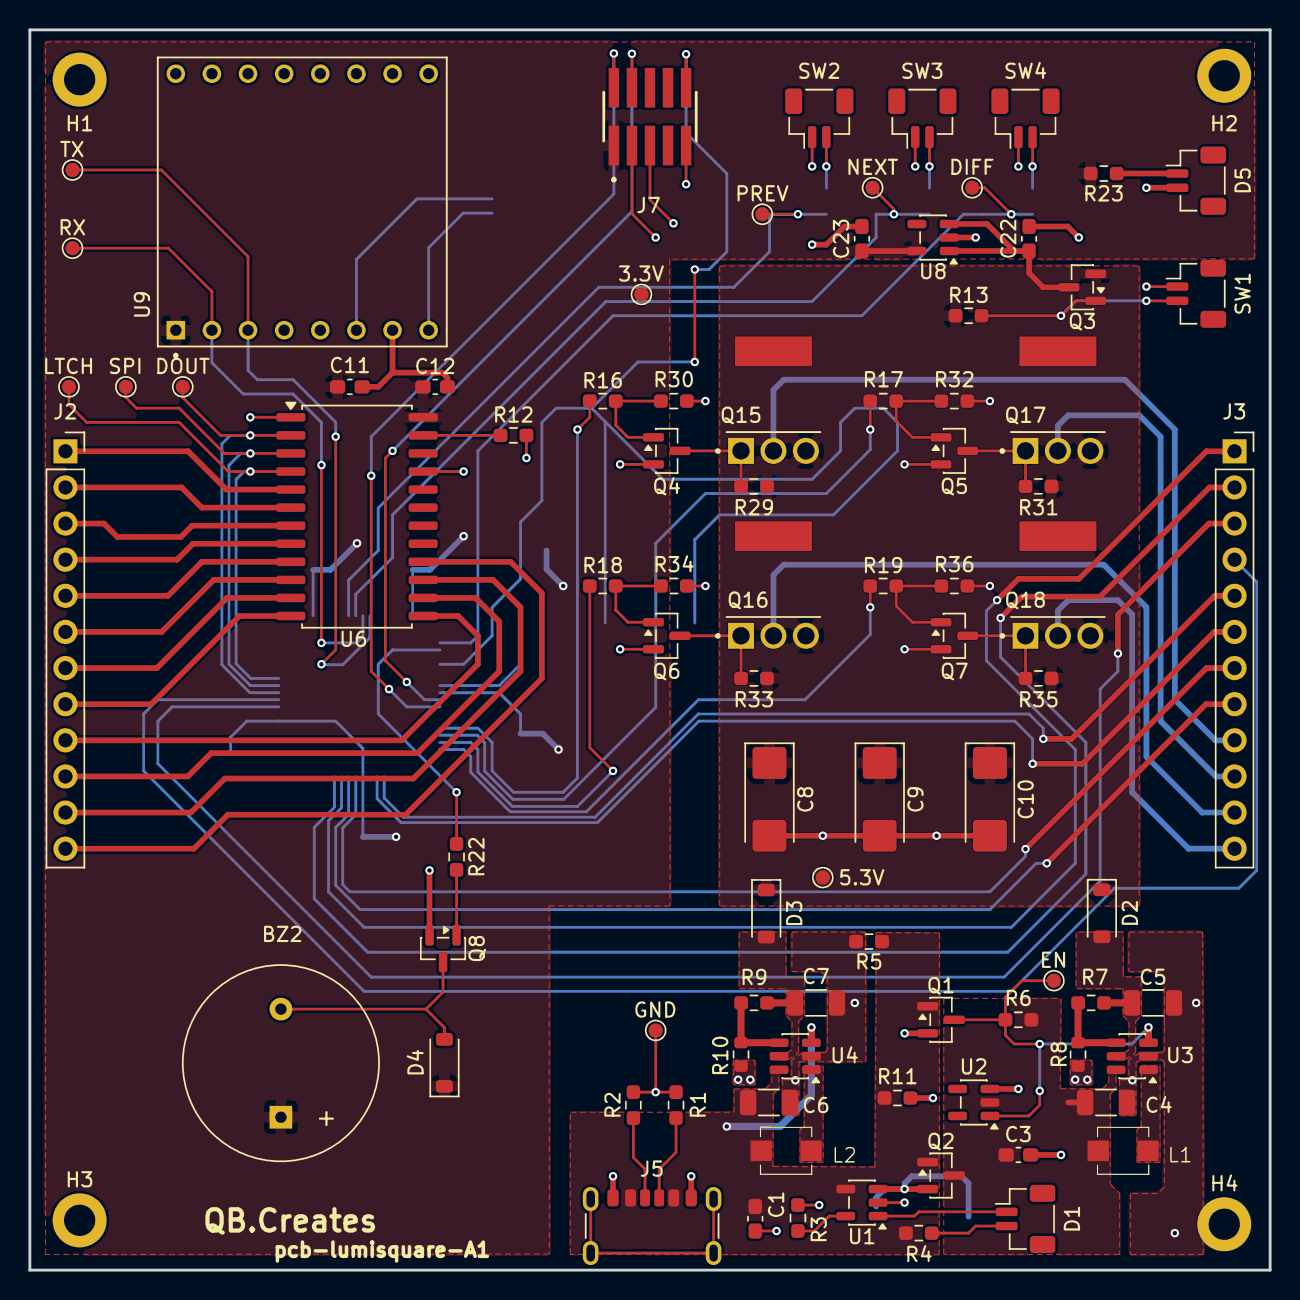
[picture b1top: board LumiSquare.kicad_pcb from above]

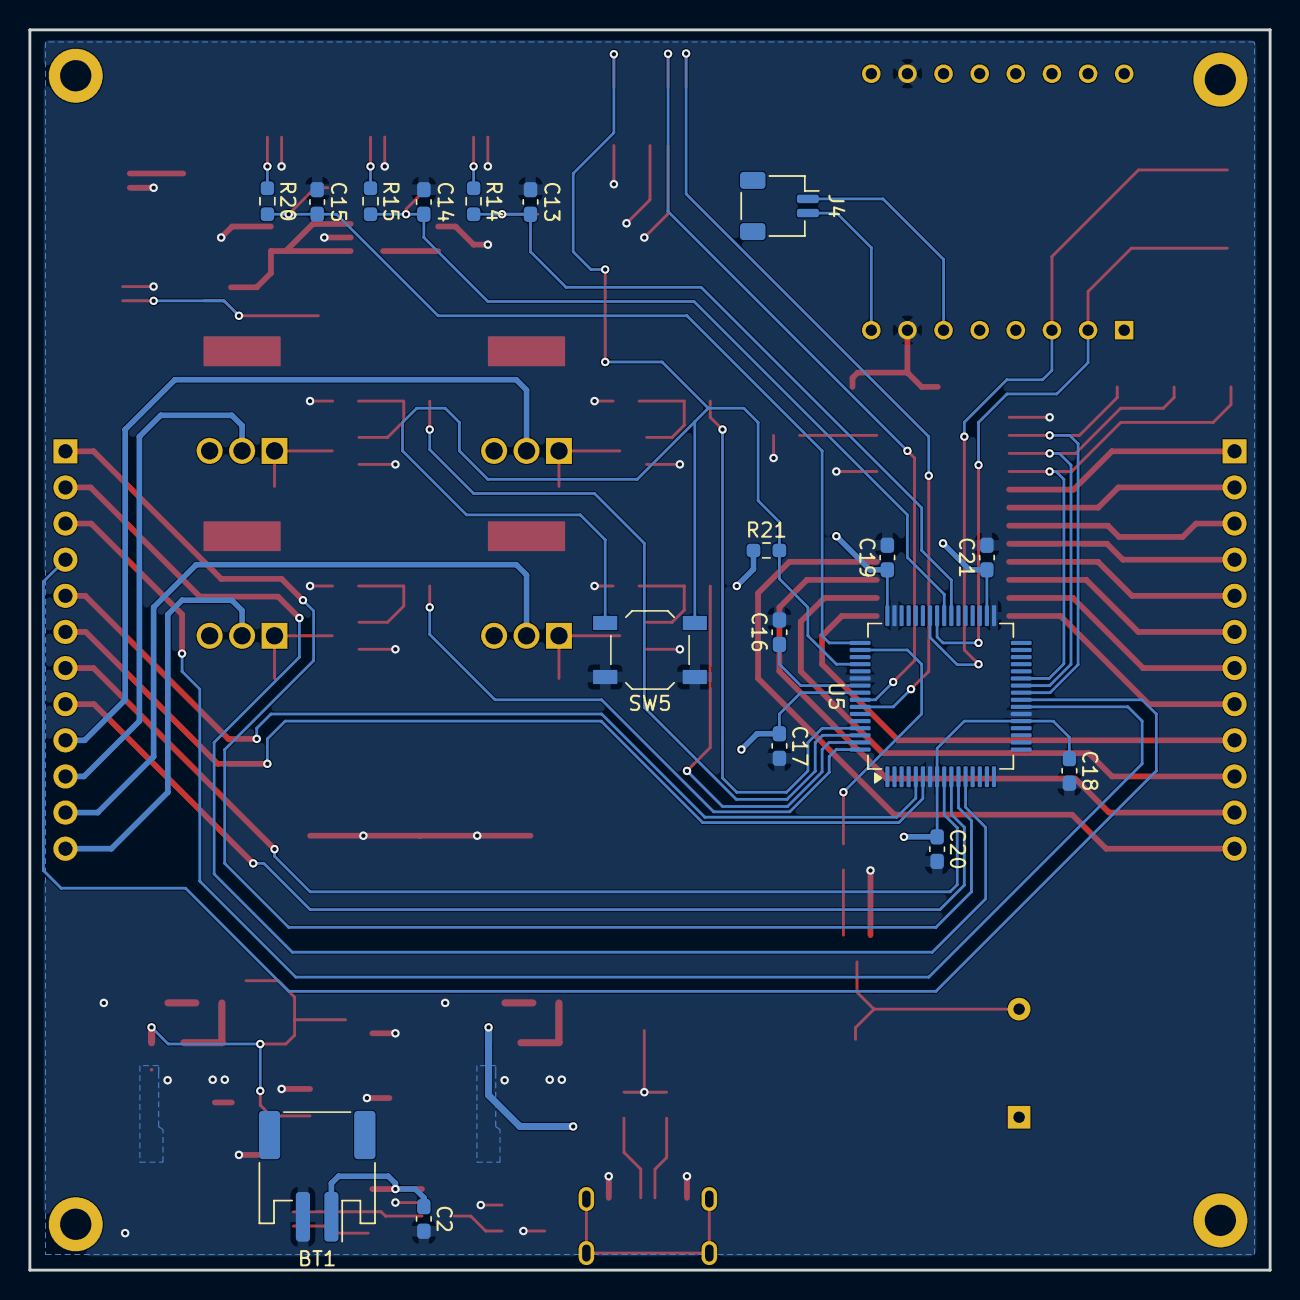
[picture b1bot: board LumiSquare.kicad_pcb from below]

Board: 2 copper layers, 87.2 x 87.2 mm, 109 parts (18 on the bottom side), 78 nets.

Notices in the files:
README.md:
License:
See [LICENSE](LICENSE) for details.
| | `CC0` sets the period and therefore the pitch: frequency = 187500 / (CC0 + 1)
| | `CC1` is set to `CC0 / 2` for a fixed 50 percent duty cycle
